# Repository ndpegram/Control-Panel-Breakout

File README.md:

# Simple Control Panel Breakout

This pcb allows the remote control of a point motor via 4 wires:

 1. +5v
 2. Gnd
 3. LED indicator (high/low)
 4. Pushbutton (active low)

These four wires must share a common ground with the controller. They assume that the point's position is toggled by pressing the pushbutton which is active low. The board takes the signal on the single LED wire and converts it to two LEDs to indicate whether the point is straight or thrown.

The button and LEDs can be mounted directly onto the PCB and the PCB attached to the rear of the panel using the included screw hole. In this case, through-hole (THT) LEDs are recommended. The tactile switch should have a shaft long enough to protrude through the panel fascia. Included is a drilling template (created in FreeCAD) which can be used to drill the button and LED holes. Note that surface-mount (SMD) LEDs could be used by soldering them between the LED pads on the PCB.

Alternatively, the PCB can be mounted elsewhere, and the LEDs and button connected via wires to the appropriate holes on the PCB.

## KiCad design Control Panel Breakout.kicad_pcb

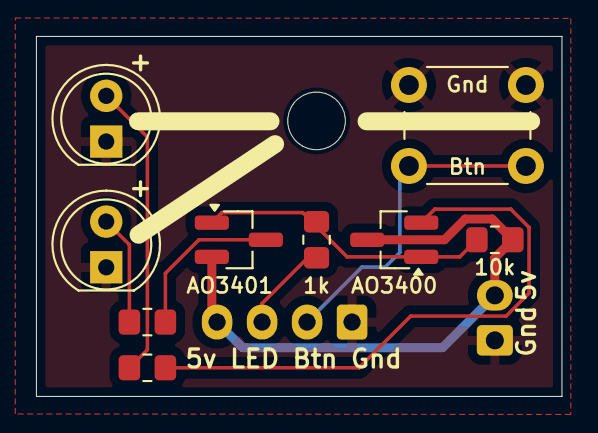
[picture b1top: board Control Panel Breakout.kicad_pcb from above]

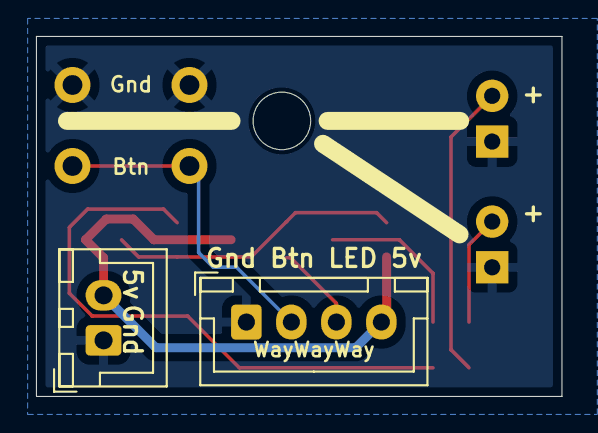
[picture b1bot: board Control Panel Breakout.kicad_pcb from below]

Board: 2 copper layers, 29.2 x 20.0 mm, 12 parts (2 on the bottom side), 9 nets.

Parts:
D1, D2: Red; LED_D5.0mm
H1: MountingHole; MountingHole_3.2mm_M3
J1: Conn_01x04_Pin; JST_XH_B4B-XH-A_1x04_P2.50mm_Vertical
J2: Conn_01x02_Pin; JST_XH_B2B-XH-A_1x02_P2.50mm_Vertical
Q1: AO3400A; SOT-23_Handsoldering
Q2: AO3401A; SOT-23_Handsoldering
R1: 1k; R_0805_2012Metric_Pad1.20x1.40mm_HandSolder
R2, R3: 330R; R_0805_2012Metric_Pad1.20x1.40mm_HandSolder
R4: 10k; R_0805_2012Metric_Pad1.20x1.40mm_HandSolder
SW1: SW_Push_Dual; SW_PUSH_6mm_H5mm

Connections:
+5V: J1.4, J2.2, Q1.3 (D), Q2.2 (S), R4.2
/Diverging: Q2.3 (D), R3.1
/MimicButton: J1.2, SW1.2
/MimicLED: J1.3, R1.2
/Straight: Q1.2 (S), R2.1
/signal: Q1.1 (G), Q2.1 (G), R1.1, R4.1
GND: D1.1 (K), D2.1 (K), J1.1, J2.1, SW1.1
unnamed: D1.2 (A), R2.2
unnamed: D2.2 (A), R3.2

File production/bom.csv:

Designator,Footprint,Quantity,Value,LCSC Part #
"D1, D2",LED_D5.0mm,2,Red,
J1,JST_XH_B4B-XH-A_1x04_P2.50mm_Vertical,1,Conn_01x04_Pin,
J2,JST_XH_B2B-XH-A_1x02_P2.50mm_Vertical,1,Conn_01x02_Pin,
Q1,SOT-23_Handsoldering,1,AO3400A,
Q2,SOT-23_Handsoldering,1,AO3401A,
R1,0805,1,1k,
"R2, R3",0805,2,330R,
R4,0805,1,10k,
SW1,SW_PUSH_6mm_H5mm,1,SW_Push_Dual,

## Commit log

2025-10-21 Create stuff
2025-10-22 Deleted stuff
2025-10-22 Create THT version of schematic, PCB and template
2025-10-22 remove files
